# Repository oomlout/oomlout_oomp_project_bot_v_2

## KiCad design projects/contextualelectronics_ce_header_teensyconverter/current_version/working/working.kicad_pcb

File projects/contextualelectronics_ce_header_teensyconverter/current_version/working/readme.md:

# ce_header
 
## summary 
* id: contextualelectronics_ce_header_teensyconverter
* user: contextualelectronics
* name: ce_header
* board: teensyconverter
* repo: https://github.com/ContextualElectronics/CE-Header
* src_file_repo_kicad_pcb: TeensyConverter/TeensyConverter.kicad_pcb
* src_file_repo_kicad_pcb_link: https://github.com/ContextualElectronics/CE-Header/tree/master/TeensyConverter/TeensyConverter.kicad_pcb

* src_file_repo_sch: TeensyConverter/TeensyConverter.sch
* src_file_repo_sch_link: https://github.com/ContextualElectronics/CE-Header/tree/master/TeensyConverter/TeensyConverter.sch
* full details link: https://github.com/oomlout/oomlout_oomp_project_bot_v_2/tree/main/projects/contextualelectronics_ce_header_teensyconverter/current_version/working  

## schematic  
  
[schematic (pdf)](working_schematic.pdf) 

## pcb  

[board (pdf)](working.pdf)  

## working_bom
| Id | Designator | Footprint | Quantity | Designation | Supplier and ref |  | None | 
| --- | --- | --- | --- | --- | --- | --- | --- | 
| 1 | P1 | Pin_Header_Straight_1x03_Pitch2.54mm | 1 | CONN_01X03 |  |  | [''] | 
| 2 | R1,R2 | R_0805_HandSoldering | 2 | 0 |  |  | [''] | 
| 3 | U2 | CE_Header | 1 | CE_HEADER |  |  | [''] | 
| 4 | U1 | Teensy-32 | 1 | Teensy-3.2 |  |  | [''] | 

## bom_schematic
| Ref | Qnty | Value | Cmp name | Footprint | Description | Vendor | DNP | 
| --- | --- | --- | --- | --- | --- | --- | --- | 
| P1 | 1 | CONN_01X03 | CONN_01X03 | Pin_Headers:Pin_Header_Straight_1x03_Pitch2.54mm |  |  |  | 
| R1, R2 | 2 | 0 | R | Resistors_SMD:R_0805_HandSoldering |  |  |  | 
| U1 | 1 | Teensy-3.2 | Teensy-3.2 | TeensyConverter:Teensy-32 |  |  |  | 
| U2 | 1 | CE_HEADER | CE_HEADER | TeensyConverter:CE_Header |  |  |  |

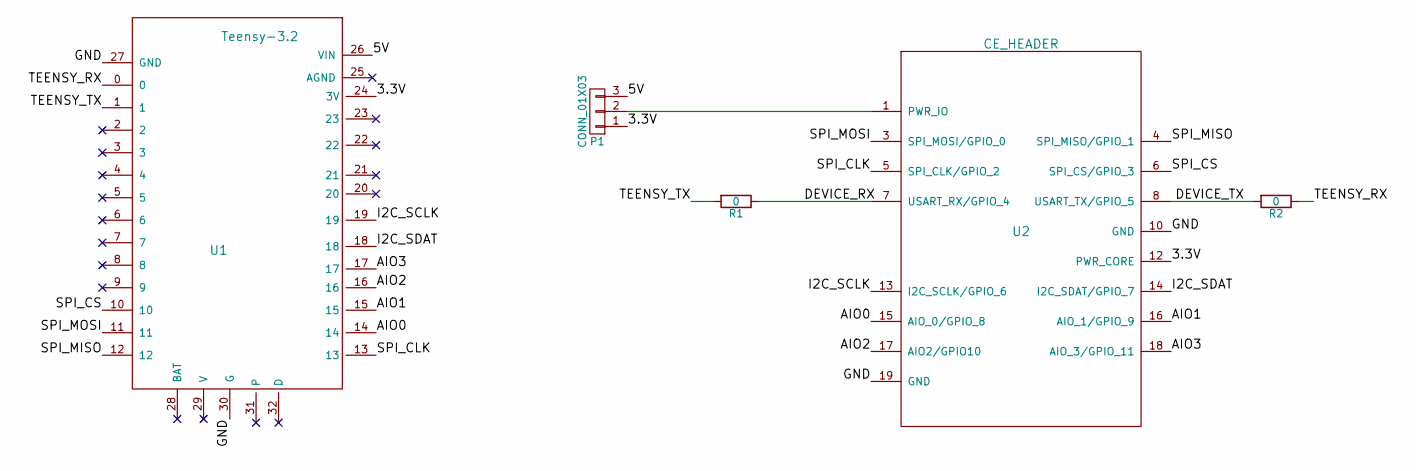
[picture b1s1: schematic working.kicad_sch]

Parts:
P1: CONN_01X03; Pin_Header_Straight_1x03_Pitch2.54mm
R1, R2: 0; R_0805_HandSoldering
U1: Teensy-3.2; Teensy-32
U2: CE_HEADER; CE_Header

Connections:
/3.3V: P1.1, U1.24 (3V), U2.12 (PWR_CORE)
/5V: P1.3, U1.26 (VIN)
/AIO0: U1.14, U2.15 (AIO_0/GPIO_8)
/AIO1: U1.15, U2.16 (AIO_1/GPIO_9)
/AIO2: U1.16, U2.17 (AIO2/GPIO10)
/AIO3: U1.17, U2.18 (AIO_3/GPIO_11)
/DEVICE_RX: R1.1, U2.7 (USART_RX/GPIO_4)
/DEVICE_TX: R2.2, U2.8 (USART_TX/GPIO_5)
/GND: U1.27 (GND), U1.30 (G), U2.10 (GND), U2.19 (GND)
/I2C_SCLK: U1.19, U2.13 (I2C_SCLK/GPIO_6)
/I2C_SDAT: U1.18, U2.14 (I2C_SDAT/GPIO_7)
/SPI_CLK: U1.13, U2.5 (SPI_CLK/GPIO_2)
/SPI_CS: U1.10, U2.6 (SPI_CS/GPIO_3)
/SPI_MISO: U1.12, U2.4 (SPI_MISO/GPIO_1)
/SPI_MOSI: U1.11, U2.3 (SPI_MOSI/GPIO_0)
/TEENSY_RX: R2.1, U1.0
/TEENSY_TX: R1.2, U1.1
unnamed: P1.2, U2.1 (PWR_IO)

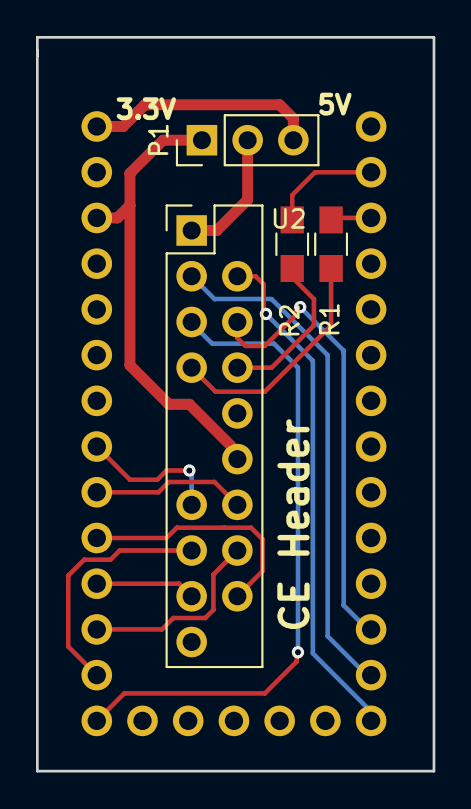
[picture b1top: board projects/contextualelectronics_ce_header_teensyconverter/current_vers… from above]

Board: 2 copper layers, 22.0 x 40.8 mm, 5 parts (1 on the bottom side), 18 nets.

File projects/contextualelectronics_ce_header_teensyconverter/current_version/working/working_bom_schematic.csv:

"Source:","C:\gh\oomlout_oomp_project_bot_v_2\projects\contextualelectronics_ce_header_teensyconverter\current_version\working\working.kicad_sch"
"Date:","19/09/2023 16:07:24"
"Tool:","Eeschema 7.0.6"
"Generator:","C:/Program Files/KiCad/7.0/bin/scripting/plugins/bom_csv_grouped_by_value_with_fp.py"
"Component Count:","5"
"Ref","Qnty","Value","Cmp name","Footprint","Description","Vendor","DNP"
"P1","1","CONN_01X03","CONN_01X03","Pin_Headers:Pin_Header_Straight_1x03_Pitch2.54mm","","",""
"R1, R2","2","0","R","Resistors_SMD:R_0805_HandSoldering","","",""
"U1","1","Teensy-3.2","Teensy-3.2","TeensyConverter:Teensy-32","","",""
"U2","1","CE_HEADER","CE_HEADER","TeensyConverter:CE_Header","","",""

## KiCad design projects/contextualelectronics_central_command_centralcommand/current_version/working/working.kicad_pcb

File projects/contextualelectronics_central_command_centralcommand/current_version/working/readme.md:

# central_command
 
## summary 
* id: contextualelectronics_central_command_centralcommand
* user: contextualelectronics
* name: central_command
* board: centralcommand
* repo: https://github.com/ContextualElectronics/Central-Command
* src_file_repo_kicad_pcb: Hardware/CentralCommand.kicad_pcb
* src_file_repo_kicad_pcb_link: https://github.com/ContextualElectronics/Central-Command/tree/master/Hardware/CentralCommand.kicad_pcb

* src_file_repo_sch: Hardware/CentralCommand.sch
* src_file_repo_sch_link: https://github.com/ContextualElectronics/Central-Command/tree/master/Hardware/CentralCommand.sch
* full details link: https://github.com/oomlout/oomlout_oomp_project_bot_v_2/tree/main/projects/contextualelectronics_central_command_centralcommand/current_version/working  

## schematic  
  
[schematic (pdf)](working_schematic.pdf) 

## pcb  

[board (pdf)](working.pdf)  

## working_bom
| Id | Designator | Footprint | Quantity | Designation | Supplier and ref |  | None | 
| --- | --- | --- | --- | --- | --- | --- | --- | 
| 1 | D301,D302 | Diode-SMA_Standard | 2 | D_Schottky |  |  | [''] | 
| 2 | D303,D304 | LED-0805 | 2 | LED |  |  | [''] | 
| 3 | L301 | Neosid_Inductor_SM1206 | 1 | FERRITE |  |  | [''] | 
| 4 | P101,P102 | Pin_Header_Straight_1x10 | 2 | CONN_01X10 |  |  | [''] | 
| 5 | P103,P105 | Pin_Header_Straight_1x04 | 2 | CONN_01X04 |  |  | [''] | 
| 6 | P104,P106,P302 | Pin_Header_Straight_1x02 | 3 | CONN_01X02 |  |  | [''] | 
| 7 | P201 | Pin_Header_Straight_1x06 | 1 | CONN_01X06 |  |  | [''] | 
| 8 | P204 | Pin_Header_Straight_1x03 | 1 | CONN_01X03 |  |  | [''] | 
| 9 | U101 | LQFP-48_7x7mm_Pitch0.5mm | 1 | STM32F030C8 |  |  | [''] | 
| 10 | U301 | SOT-23 | 1 | MCP1700T-3302E/TT_ |  |  | [''] | 
| 11 | U302 | QFN-32-1EP_5x5mm_Pitch0.5mm | 1 | FT232RQ |  |  | [''] | 
| 12 | Y101 | Crystal_HC49-U_Vertical | 1 | Crystal |  |  | [''] | 
| 13 | P301 | 10118193 | 1 | USB_B |  |  | [''] | 
| 14 | P202,P203 | Grove-2mm | 2 | CONN_01X04 |  |  | [''] | 
| 15 | SW201 | FSM2JSMAA-ND | 1 | FSM2JSMAA-ND |  |  | [''] | 
| 16 | REF**,REF**,REF**,REF** | MountingHole_3mm | 4 | MountingHole_3mm |  |  | [''] | 
| 17 | C101,C201 | C_0805 | 2 | C |  |  | [''] | 
| 18 | C102,C103 | C_0805 | 2 | 20P |  |  | [''] | 
| 19 | C301,C302,C304,C104,C107 | C_0805 | 5 | .1U |  |  | [''] | 
| 20 | C303 | C_1210 | 1 | 4.7U |  |  | [''] | 
| 21 | C305,C306 | C_1210 | 2 | 10U |  |  | [''] | 
| 22 | L101 | Neosid_Inductor_SM1206 | 1 | INDUCTOR |  |  | [''] | 
| 23 | R201,R202,R204 | R_0805 | 3 | R |  |  | [''] | 
| 24 | R203,R301,R302,R303,R206,R207,R208,R209 | R_0805 | 8 | 0 |  |  | [''] | 
| 25 | R304,R305 | R_0805 | 2 | NOPE |  |  | [''] | 
| 26 | R306,R307 | R_0805 | 2 | 270 |  |  | [''] | 
| 27 | C105,C108 | C_1206 | 2 | 1U |  |  | [''] | 
| 28 | C106,C109 | C_1206 | 2 | 10U |  |  | [''] | 
| 29 | G*** | CClogo-small | 1 | LOGO |  |  | [''] | 

## bom_schematic
| Ref | Qnty | Value | Cmp name | Footprint | Description | Vendor | DNP | 
| --- | --- | --- | --- | --- | --- | --- | --- | 
| C101, C104, C107 | 3 | .1U | C | Capacitors_SMD:C_0805 |  |  |  | 
| C102, C103 | 2 | 20P | C | Capacitors_SMD:C_0805 |  |  |  | 
| C105, C108 | 2 | 1U | C | Capacitors_SMD:C_1206 |  |  |  | 
| C106, C109 | 2 | 10U | C | Capacitors_SMD:C_1206 |  |  |  | 
| L101 | 1 | 10uH | INDUCTOR | Inductors_NEOSID:Neosid_Inductor_SM1206 |  |  |  | 
| P101, P102 | 2 | CONN_01X10 | CONN_01X10 | Pin_Headers:Pin_Header_Straight_1x10 |  |  |  | 
| P103, P105 | 2 | CONN_01X04 | CONN_01X04 | Pin_Headers:Pin_Header_Straight_1x04 |  |  |  | 
| P104, P106 | 2 | CONN_01X02 | CONN_01X02 | Pin_Headers:Pin_Header_Straight_1x02 |  |  |  | 
| U101 | 1 | STM32F030C8 | STM32F030C8 | Housings_QFP:LQFP-48_7x7mm_Pitch0.5mm |  |  |  | 
| Y101 | 1 | Crystal | Crystal | Crystals:Crystal_HC49-U_Vertical |  |  |  | 

## mounting_holes
| x | y | package | value | ref | size | 
| --- | --- | --- | --- | --- | --- | 
| 0.06 | 44.17 | MountingHole_3mm | MountingHole_3mm | REF** | m3 | 
| 0.0 | 0.0 | MountingHole_3mm | MountingHole_3mm | REF** | m3 | 
| 44.23 | 0.0 | MountingHole_3mm | MountingHole_3mm | REF** | m3 | 
| 44.18 | 44.15 | MountingHole_3mm | MountingHole_3mm | REF** | m3 |

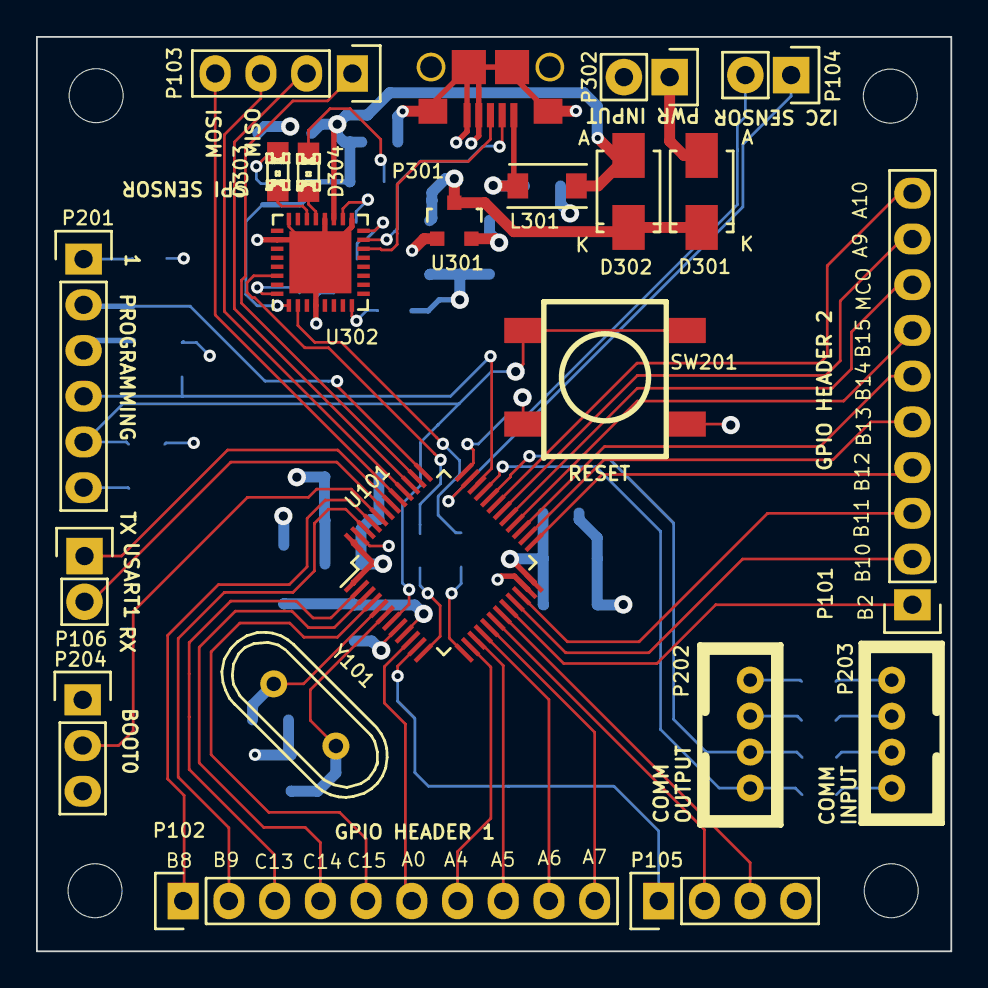
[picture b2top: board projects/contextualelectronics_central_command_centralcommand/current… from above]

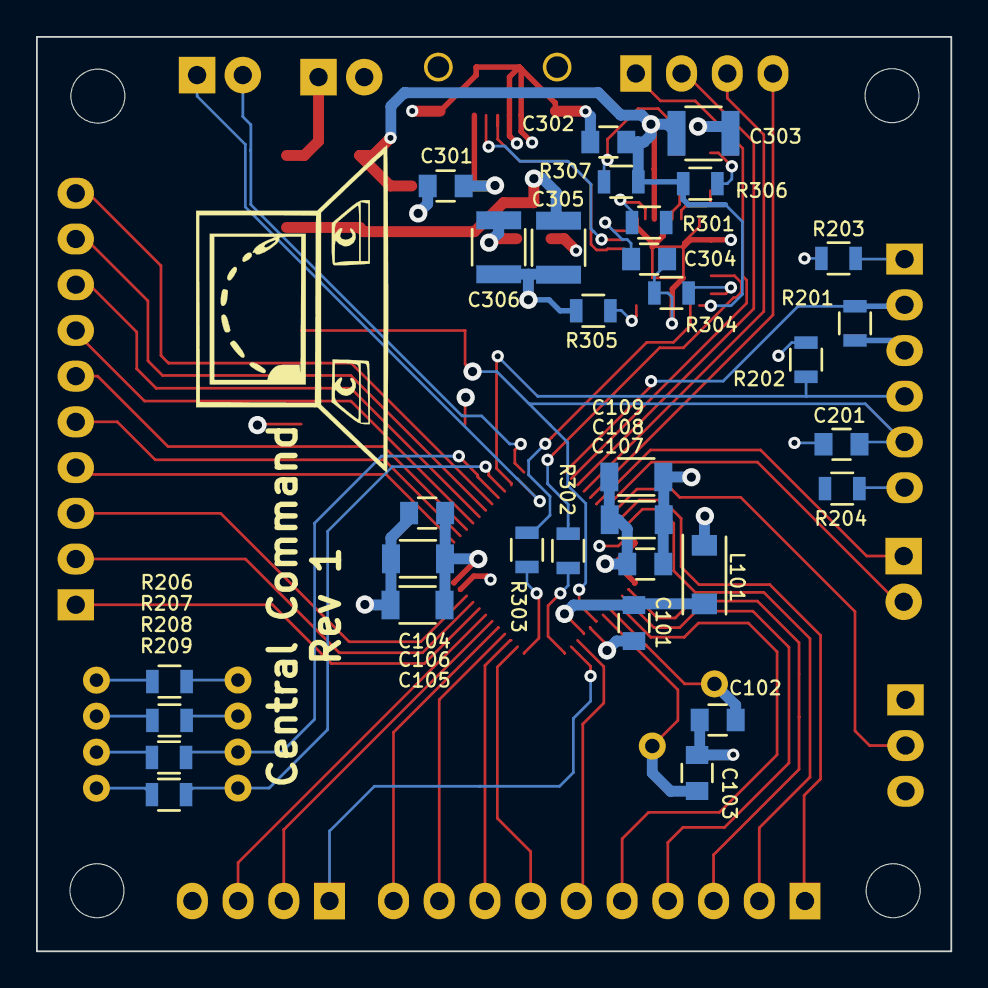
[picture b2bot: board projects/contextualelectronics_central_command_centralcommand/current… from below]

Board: 4 copper layers, 50.8 x 50.8 mm, 54 parts (32 on the bottom side), 66 nets.

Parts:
C101, C201: C; C_0805
C102, C103: 20P; C_0805
C104, C107, C301, C302, C304: .1U; C_0805
C105, C108: 1U; C_1206
C106, C109: 10U; C_1206
C303: 4.7U; C_1210
C305, C306: 10U; C_1210
D301, D302: D_Schottky; Diode-SMA_Standard
D303, D304: LED; LED-0805
L101: INDUCTOR; Neosid_Inductor_SM1206
L301: FERRITE; Neosid_Inductor_SM1206
P101, P102: CONN_01X10; Pin_Header_Straight_1x10
P103, P105: CONN_01X04; Pin_Header_Straight_1x04
P104, P106, P302: CONN_01X02; Pin_Header_Straight_1x02
P201: CONN_01X06; Pin_Header_Straight_1x06
P202, P203: CONN_01X04; Grove-2mm
P204: CONN_01X03; Pin_Header_Straight_1x03
P301: USB_B; 10118193
R201, R202, R204: R; R_0805
R203, R206, R207, R208, R209, R301, R302, R303: 0; R_0805
R304, R305: NOPE; R_0805
R306, R307: 270; R_0805
SW201: FSM2JSMAA-ND
U101: STM32F030C8; LQFP-48_7x7mm_Pitch0.5mm
U301: MCP1700T-3302E/TT_; SOT-23
U302: FT232RQ; QFN-32-1EP_5x5mm_Pitch0.5mm
Y101: Crystal; Crystal_HC49-U_Vertical

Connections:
/ADC_IN1: P105.1, U101.11
/ADC_IN8: P105.2, U101.18
/ADC_IN9: P105.3, U101.19
/Comm/BOOT0: P204.2, U101.44
/Comm/NRST: C201.1, P201.5, SW201.1, U101.7
/Comm/PWR: C104.1, C105.1, C106.1, C107.1, C108.1, C109.1, C306.1, L101.1, P202.2, P204.1, R202.1, R203.1, R207.1, U101.1, U101.24, U101.48, U301.2
/Comm/SCL: P202.3, R208.1, U101.32
/Comm/SDA: P202.4, R209.1, U101.33
/Comm/SWCLK: P201.2, R201.1, U101.37
/Comm/SWIO: P201.4, R202.2, U101.34
/I2C1_SCL: P104.2, U101.36
/I2C1_SDA: P104.1, U101.35
/MCO: P101.8, U101.29
/PA0: P102.6, U101.10
/PA4: P102.7, U101.14
/PA5: P102.8, U101.15
/PA6: P102.9, U101.16
/PA7: P102.10, U101.17
/PA9: P101.9, U101.30
/PA10: P101.10, U101.31
/PB2: P101.1, U101.20
/PB8: P102.1, U101.45
/PB9: P102.2, U101.46
/PB10: P101.2, U101.21
/PB11: P101.3, U101.22
/PB12: P101.4, U101.25
/PB13: P101.5, U101.26
/PB14: P101.6, U101.27
/PB15: P101.7, U101.28
/PC13: P102.3, U101.2
/PC14: P102.4, U101.3
/PC15: P102.5, U101.4
/Power/RXD: R303.1, U101.13
/Power/TXD: R302.1, U101.12
/Power/VCCIO: C302.1, C303.1, D302.2, L301.2, R306.1, R307.1, U302.1, U302.19
/SPI1_MISO: P103.3, U101.40
/SPI1_MOSI: P103.4, U101.41
/SPI1_NSS: P103.1, U101.38
/SPI1_SCK: P103.2, U101.39
/USART1_RX: P106.2, U101.43
/USART1_TX: P106.1, U101.42
/VDDA: C101.1, L101.2, U101.9
GND: C101.2, C102.1, C103.1, C104.2, C105.2, C106.2, C107.2, C108.2, C109.2, C201.2, C301.2, C302.2, C303.2, C304.2, C305.2, C306.2, P105.4, P201.3, P202.1, P204.3, P301.4, P301.5, P301.6, P301.7, P301.8, P301.9, P302.2, R201.2, R206.1, R304.1, R305.1, SW201.2, U101.8, U101.23, U101.47, U301.1, U302.4, U302.17, U302.20, U302.24, U302.26, U302.33
unnamed: C102.2, U101.5, Y101.1
unnamed: C103.2, U101.6, Y101.2
unnamed: C301.1, L301.1, P301.1
unnamed: C304.1, U302.16
unnamed: C305.1, D301.1, D302.1, U301.3
unnamed: D301.2, P302.1
unnamed: D303.1, U302.22
unnamed: D303.2, R306.2
unnamed: D304.1, U302.21
unnamed: D304.2, R307.2
unnamed: P201.1, R203.2
unnamed: P201.6, R204.1
unnamed: P203.1, R209.2
unnamed: P203.2, R208.2
unnamed: P203.3, R207.2
unnamed: P203.4, R206.2
unnamed: P301.2, U302.15
unnamed: P301.3, U302.14
unnamed: R301.1, U302.18
unnamed: R302.2, U302.30
unnamed: R303.2, U302.2
unnamed: R304.2, U302.32
unnamed: R305.2, U302.8

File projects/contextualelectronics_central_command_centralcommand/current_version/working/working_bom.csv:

"Id";"Designator";"Footprint";"Quantity";"Designation";"Supplier and ref";
1;"D301,D302";"Diode-SMA_Standard";2;"D_Schottky";;;
2;"D303,D304";"LED-0805";2;"LED";;;
3;"L301";"Neosid_Inductor_SM1206";1;"FERRITE";;;
4;"P101,P102";"Pin_Header_Straight_1x10";2;"CONN_01X10";;;
5;"P103,P105";"Pin_Header_Straight_1x04";2;"CONN_01X04";;;
6;"P104,P106,P302";"Pin_Header_Straight_1x02";3;"CONN_01X02";;;
7;"P201";"Pin_Header_Straight_1x06";1;"CONN_01X06";;;
8;"P204";"Pin_Header_Straight_1x03";1;"CONN_01X03";;;
9;"U101";"LQFP-48_7x7mm_Pitch0.5mm";1;"STM32F030C8";;;
10;"U301";"SOT-23";1;"MCP1700T-3302E/TT_";;;
11;"U302";"QFN-32-1EP_5x5mm_Pitch0.5mm";1;"FT232RQ";;;
12;"Y101";"Crystal_HC49-U_Vertical";1;"Crystal";;;
13;"P301";"10118193";1;"USB_B";;;
14;"P202,P203";"Grove-2mm";2;"CONN_01X04";;;
15;"SW201";"FSM2JSMAA-ND";1;"FSM2JSMAA-ND";;;
16;"REF**,REF**,REF**,REF**";"MountingHole_3mm";4;"MountingHole_3mm";;;
17;"C101,C201";"C_0805";2;"C";;;
18;"C102,C103";"C_0805";2;"20P";;;
19;"C301,C302,C304,C104,C107";"C_0805";5;".1U";;;
20;"C303";"C_1210";1;"4.7U";;;
21;"C305,C306";"C_1210";2;"10U";;;
22;"L101";"Neosid_Inductor_SM1206";1;"INDUCTOR";;;
23;"R201,R202,R204";"R_0805";3;"R";;;
24;"R203,R301,R302,R303,R206,R207,R208,R209";"R_0805";8;"0";;;
25;"R304,R305";"R_0805";2;"NOPE";;;
26;"R306,R307";"R_0805";2;"270";;;
27;"C105,C108";"C_1206";2;"1U";;;
28;"C106,C109";"C_1206";2;"10U";;;
29;"G***";"CClogo-small";1;"LOGO";;;

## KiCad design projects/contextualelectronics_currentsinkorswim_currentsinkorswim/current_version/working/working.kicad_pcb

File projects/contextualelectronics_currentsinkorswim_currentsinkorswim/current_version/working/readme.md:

# currentsinkorswim
 
## summary 
* id: contextualelectronics_currentsinkorswim_currentsinkorswim
* user: contextualelectronics
* name: currentsinkorswim
* board: currentsinkorswim
* repo: https://github.com/ContextualElectronics/CurrentSinkOrSwim
* src_file_repo_kicad_pcb: CurrentSinkOrSwim.kicad_pcb
* src_file_repo_kicad_pcb_link: https://github.com/ContextualElectronics/CurrentSinkOrSwim/tree/master/CurrentSinkOrSwim.kicad_pcb

* src_file_repo_sch: 
* src_file_repo_sch_link: https://github.com/ContextualElectronics/CurrentSinkOrSwim/tree/master/
* full details link: https://github.com/oomlout/oomlout_oomp_project_bot_v_2/tree/main/projects/contextualelectronics_currentsinkorswim_currentsinkorswim/current_version/working  

## schematic  
  
[schematic (pdf)](working_schematic.pdf) 

## pcb  

[board (pdf)](working.pdf)  

## working_bom
| Id | Designator | Footprint | Quantity | Designation | Supplier and ref |  | None | 
| --- | --- | --- | --- | --- | --- | --- | --- | 
| 1 | D201 | SOD-523 | 1 | DIODE |  |  | [''] | 
| 2 | Q401 | TO-220_FET-GDS_Vertical | 1 | BUK9575 |  |  | [''] | 
| 3 | R201 | SMD-0805 | 1 | 28.7K |  |  | [''] | 
| 4 | R202 | SMD-0805 | 1 | 9K |  |  | [''] | 
| 5 | R301 | SMD-0805 | 1 | 0 |  |  | [''] | 
| 6 | R302 | SMD-0805 | 1 | 27K |  |  | [''] | 
| 7 | R403 | Resistor_Horizontal_RM15mm | 1 | .1 |  |  | [''] | 
| 8 | U201 | SOIC-8-N | 1 | LMV358 |  |  | [''] | 
| 9 | U301 | SOIC-8-N | 1 | LM2931D-R |  |  | [''] | 
| 10 | P1 | FA-T220-38E | 1 | CONN_01X01 |  |  | [''] | 
| 11 | P101,P103 | Terminal_Block_200_mil | 2 | CONN_01X02 |  |  | [''] | 
| 12 | P102 | Pin_Header_Straight_1x03 | 1 | CONN_01X03 |  |  | [''] | 
| 13 | RV201,RV401 | P090L-02F25BR10K | 2 | 10K |  |  | [''] | 
| 14 | R203,R402 | SMD-0805 | 2 | 1K |  |  | [''] | 
| 15 | R303 | SMD-0805 | 1 | 21.6K |  |  | [''] | 
| 16 | G*** | CSOS | 1 | LOGO |  |  | [''] | 
| 17 | C201,C301,C302 | SMD-0805 | 3 | C |  |  | [''] | 
| 18 | R401 | SMD-0805 | 1 | 68K |  |  | [''] | 

## bom_schematic
| Ref | Qnty | Value | Cmp name | Footprint | Description | Vendor | DNP | 
| --- | --- | --- | --- | --- | --- | --- | --- | 
| P101, P103 | 2 | CONN_01X02 | CONN_01X02 | Current:Terminal_Block_200_mil |  |  |  | 
| P102 | 1 | CONN_01X03 | CONN_01X03 | Pin_Headers:Pin_Header_Straight_1x03 |  |  |  |

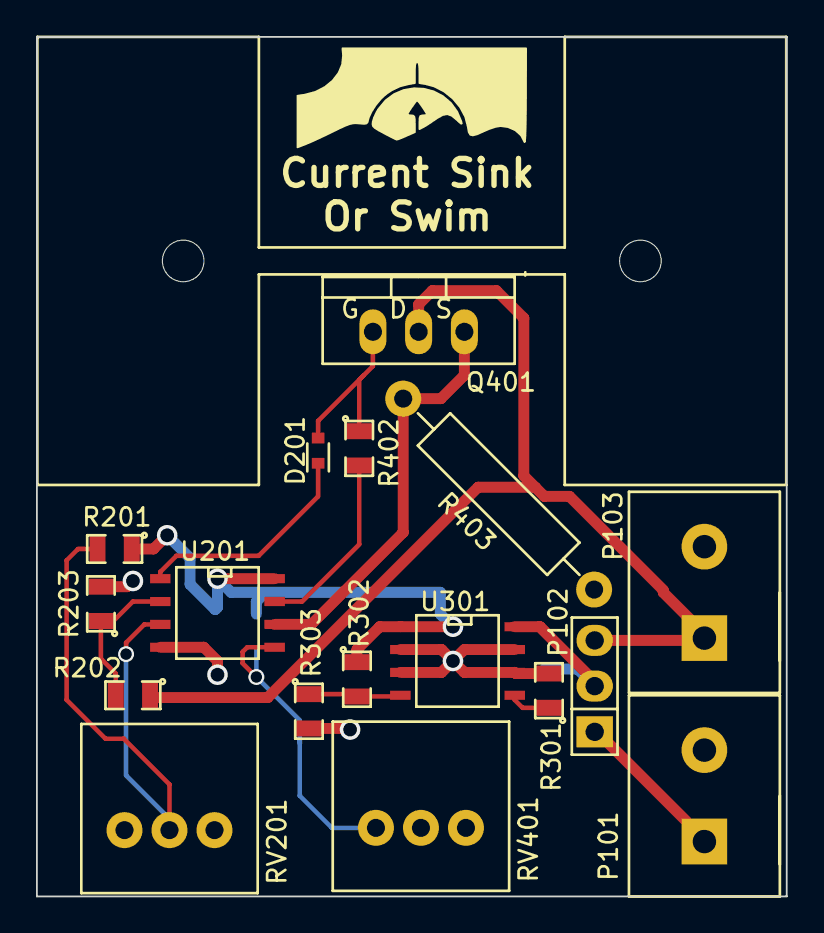
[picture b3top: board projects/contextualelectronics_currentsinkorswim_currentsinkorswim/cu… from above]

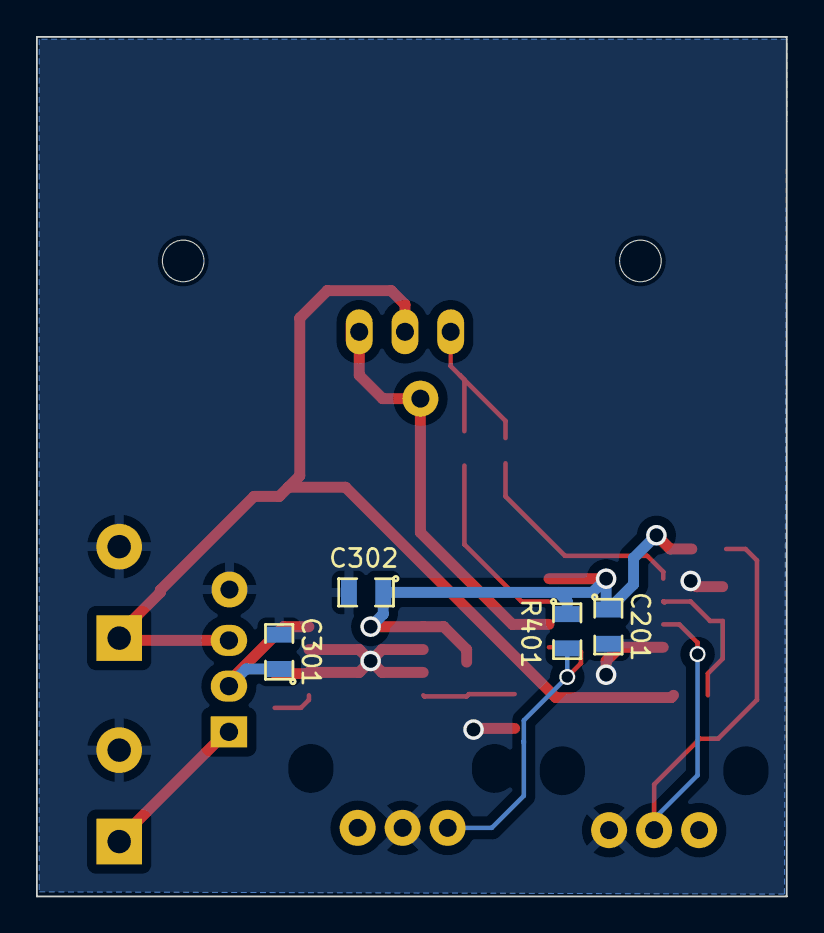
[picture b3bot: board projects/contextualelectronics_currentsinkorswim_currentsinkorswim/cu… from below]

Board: 2 copper layers, 41.7 x 47.8 mm, 22 parts (4 on the bottom side), 14 nets.

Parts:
C201, C301, C302: C; SMD-0805
D201: DIODE; SOD-523
P1: CONN_01X01; FA-T220-38E
P101, P103: CONN_01X02; Terminal_Block_200_mil
P102: CONN_01X03; Pin_Header_Straight_1x03
Q401: BUK9575; TO-220_FET-GDS_Vertical
R201: 28.7K; SMD-0805
R202: 9K; SMD-0805
R203, R402: 1K; SMD-0805
R301: 0; SMD-0805
R302: 27K; SMD-0805
R303: 21.6K; SMD-0805
R401: 68K; SMD-0805
R403: .1; Resistor_Horizontal_RM15mm
RV201, RV401: 10K; P090L-02F25BR10K
U201: LMV358; SOIC-8-N
U301: LM2931D-R; SOIC-8-N

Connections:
2.7V: C201.1, C302.1, R201.1, R302.1, R401.1, U201.8, U301.1
/Current Control/Current_Sink+: P102.3, P103.1, Q401.D, R202.1
/Current Control/FET_Gate: D201.1, Q401.G, R402.1
/Power Regulation/Vin: C301.1, P102.2, U301.8
GND: C201.2, C301.2, C302.2, P101.2, P103.2, R203.2, R301.2, R303.2, R403.2, RV201.3, RV401.2, U201.4, U301.2, U301.3, U301.6, U301.7
unnamed: D201.2, U201.1
unnamed: P101.1, P102.1
unnamed: Q401.S, R403.1, U201.6
unnamed: R201.2, RV201.2, U201.3
unnamed: R202.2, R203.1, U201.2
unnamed: R301.1, U301.5
unnamed: R302.2, R303.1, U301.4
unnamed: R401.2, RV401.1, U201.5
unnamed: R402.2, U201.7

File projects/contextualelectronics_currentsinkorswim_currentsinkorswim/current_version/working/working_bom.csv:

"Id";"Designator";"Footprint";"Quantity";"Designation";"Supplier and ref";
1;"D201";"SOD-523";1;"DIODE";;;
2;"Q401";"TO-220_FET-GDS_Vertical";1;"BUK9575";;;
3;"R201";"SMD-0805";1;"28.7K";;;
4;"R202";"SMD-0805";1;"9K";;;
5;"R301";"SMD-0805";1;"0";;;
6;"R302";"SMD-0805";1;"27K";;;
7;"R403";"Resistor_Horizontal_RM15mm";1;".1";;;
8;"U201";"SOIC-8-N";1;"LMV358";;;
9;"U301";"SOIC-8-N";1;"LM2931D-R";;;
10;"P1";"FA-T220-38E";1;"CONN_01X01";;;
11;"P101,P103";"Terminal_Block_200_mil";2;"CONN_01X02";;;
12;"P102";"Pin_Header_Straight_1x03";1;"CONN_01X03";;;
13;"RV201,RV401";"P090L-02F25BR10K";2;"10K";;;
14;"R203,R402";"SMD-0805";2;"1K";;;
15;"R303";"SMD-0805";1;"21.6K";;;
16;"G***";"CSOS";1;"LOGO";;;
17;"C201,C301,C302";"SMD-0805";3;"C";;;
18;"R401";"SMD-0805";1;"68K";;;

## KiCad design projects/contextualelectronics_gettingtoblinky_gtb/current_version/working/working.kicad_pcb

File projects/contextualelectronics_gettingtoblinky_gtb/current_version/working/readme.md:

# gettingtoblinky
 
## summary 
* id: contextualelectronics_gettingtoblinky_gtb
* user: contextualelectronics
* name: gettingtoblinky
* board: gtb
* repo: https://github.com/ContextualElectronics/GettingToBlinky
* src_file_repo_kicad_pcb: GTB.kicad_pcb
* src_file_repo_kicad_pcb_link: https://github.com/ContextualElectronics/GettingToBlinky/tree/master/GTB.kicad_pcb

* src_file_repo_sch: GTB.sch
* src_file_repo_sch_link: https://github.com/ContextualElectronics/GettingToBlinky/tree/master/GTB.sch
* full details link: https://github.com/oomlout/oomlout_oomp_project_bot_v_2/tree/main/projects/contextualelectronics_gettingtoblinky_gtb/current_version/working  

## schematic  
  
[schematic (pdf)](working_schematic.pdf) 

## pcb  

[board (pdf)](working.pdf)  

## working_bom
| Id | Designator | Footprint | Quantity | Designation | Supplier and ref |  | None | 
| --- | --- | --- | --- | --- | --- | --- | --- | 
| 1 | U1 | SO8N | 1 | 7555 |  |  | [''] | 
| 2 | R1 | SM1206 | 1 | 470K |  |  | [''] | 
| 3 | R2 | SM1206 | 1 | 1K |  |  | [''] | 
| 4 | VR1 | R1 | 1 | LDR |  |  | [''] | 
| 5 | D1 | LED-1206 | 1 | LED |  |  | [''] | 
| 6 | C1 | SM1206 | 1 | 1U |  |  | [''] | 
| 7 | BT1 | CR2032 | 1 | CR2032 |  |  | [''] | 

## bom_schematic
| Ref | Qnty | Value | Cmp name | Footprint | Description | Vendor | DNP | 
| --- | --- | --- | --- | --- | --- | --- | --- | 
| BT1 | 1 | CR2032 | BATTERY |  |  |  |  | 
| C1 | 1 | 1U | C |  |  |  |  | 
| D1 | 1 | LED | LED |  |  |  |  | 
| R1 | 1 | 470K | R |  |  |  |  | 
| R2 | 1 | 1K | R |  |  |  |  | 
| U1 | 1 | 7555 | 7555 |  |  |  |  | 
| VR1 | 1 | LDR | VR |  |  |  |  |

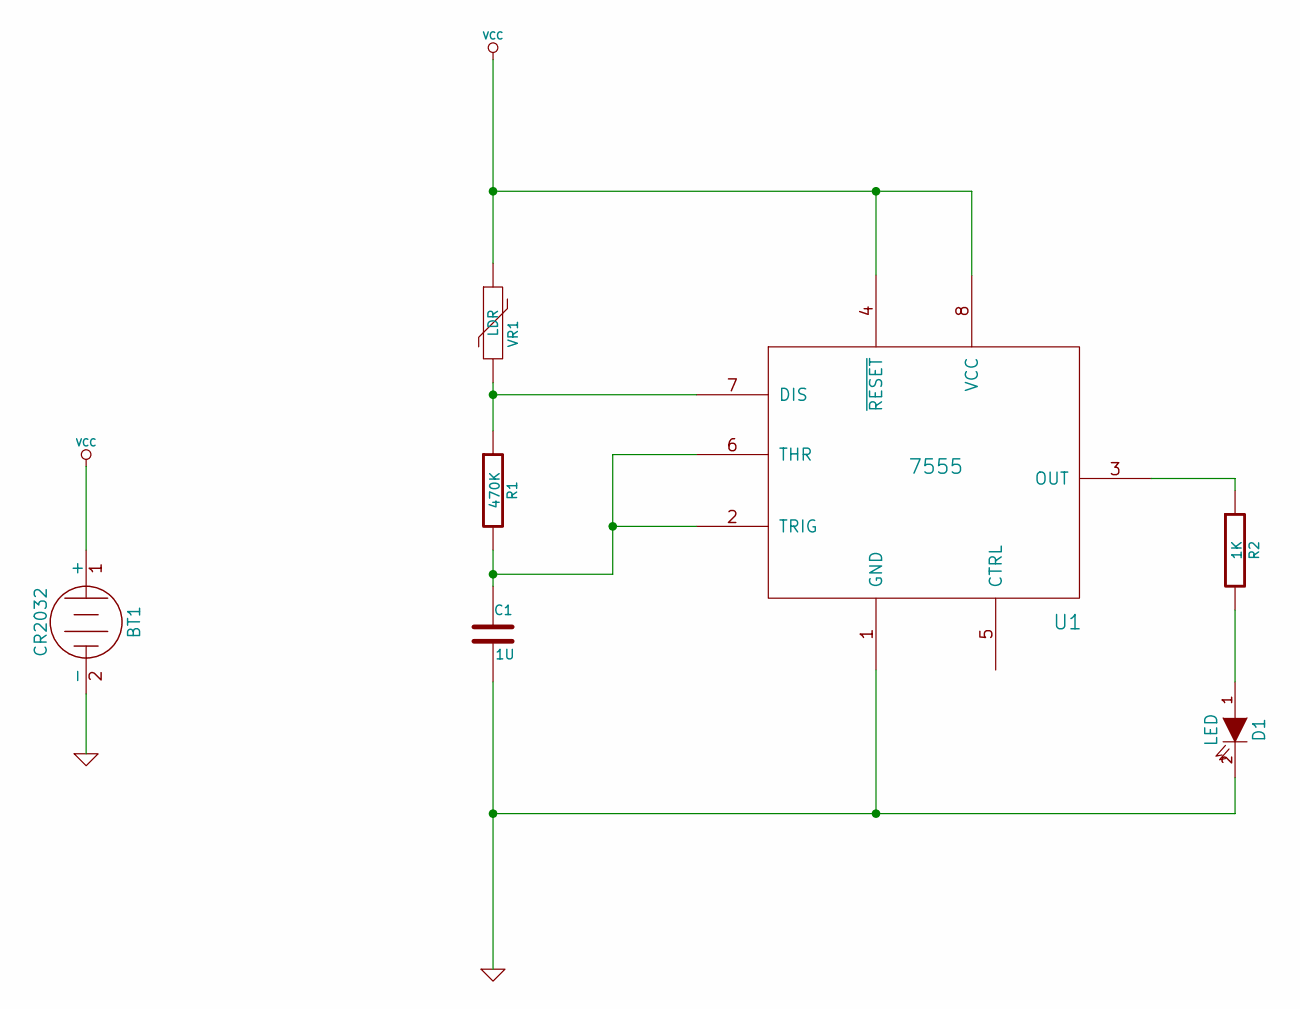
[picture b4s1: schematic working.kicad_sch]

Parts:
BT1: CR2032
C1: 1U
D1: LED
R1: 470K
R2: 1K
U1: 7555
VR1: LDR

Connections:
GND: BT1.2 (-), C1.2, D1.2 (K), U1.1 (GND)
unnamed: D1.1 (A), R2.2
unnamed: R2.1, U1.3 (OUT)
unnamed: C1.1, R1.2, U1.2 (TRIG), U1.6 (THR)
unnamed: R1.1, U1.7 (DIS), VR1.2
VCC: BT1.1 (+), U1.4 (~RESET), U1.8 (VCC), VR1.1

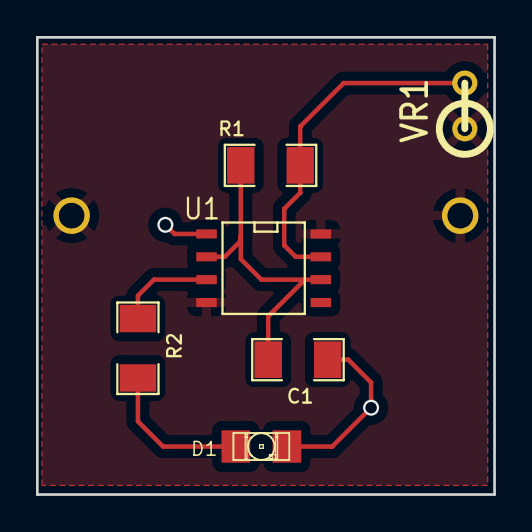
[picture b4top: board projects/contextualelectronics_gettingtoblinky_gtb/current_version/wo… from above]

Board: 2 copper layers, 25.4 x 25.4 mm, 7 parts (1 on the bottom side), 6 nets.

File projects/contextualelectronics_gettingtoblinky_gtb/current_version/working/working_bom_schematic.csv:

"Source:","C:\gh\oomlout_oomp_project_bot_v_2\projects\contextualelectronics_gettingtoblinky_gtb\current_version\working\working.kicad_sch"
"Date:","19/09/2023 16:45:40"
"Tool:","Eeschema 7.0.6"
"Generator:","C:/Program Files/KiCad/7.0/bin/scripting/plugins/bom_csv_grouped_by_value_with_fp.py"
"Component Count:","7"
"Ref","Qnty","Value","Cmp name","Footprint","Description","Vendor","DNP"
"BT1","1","CR2032","BATTERY","","","",""
"C1","1","1U","C","","","",""
"D1","1","LED","LED","","","",""
"R1","1","470K","R","","","",""
"R2","1","1K","R","","","",""
"U1","1","7555","7555","","","",""
"VR1","1","LDR","VR","","","",""

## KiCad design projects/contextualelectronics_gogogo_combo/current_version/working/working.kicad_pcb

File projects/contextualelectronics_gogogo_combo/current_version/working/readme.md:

# gogogo
 
## summary 
* id: contextualelectronics_gogogo_combo
* user: contextualelectronics
* name: gogogo
* board: combo
* repo: https://github.com/ContextualElectronics/GoGoGo
* src_file_repo_kicad_pcb: Combo.kicad_pcb
* src_file_repo_kicad_pcb_link: https://github.com/ContextualElectronics/GoGoGo/tree/master/Combo.kicad_pcb

* src_file_repo_sch: 
* src_file_repo_sch_link: https://github.com/ContextualElectronics/GoGoGo/tree/master/
* full details link: https://github.com/oomlout/oomlout_oomp_project_bot_v_2/tree/main/projects/contextualelectronics_gogogo_combo/current_version/working  

## pcb  

[board (pdf)](working.pdf)  

## working_bom
| Id | Designator | Footprint | Quantity | Designation | Supplier and ref |  | None | 
| --- | --- | --- | --- | --- | --- | --- | --- | 
| 1 | C1,C3 | C_0805 | 2 | .1U |  |  | [''] | 
| 2 | C2,C4 | C_1206 | 2 | 10U |  |  | [''] | 
| 3 | P1,P3,P1,P2 | Pin_Header_Straight_1x02 | 4 | CONN_01X02 |  |  | [''] | 
| 4 | P2 | Pin_Header_Straight_1x04 | 1 | CONN_01X04 |  |  | [''] | 
| 5 | U1 | SSOP-20 | 1 | TB6593FNG |  |  | [''] | 
| 6 | C1 | C_0805_HandSoldering | 1 | C |  |  | [''] | 
| 7 | R1 | R_0805_HandSoldering | 1 | 100 |  |  | [''] | 
| 8 | R2,R3,R4,R5 | R_0805_HandSoldering | 4 | 1K |  |  | [''] | 
| 9 | TP1 | Measurement_Point_Round-SMD-Pad_Small | 1 | OptoOut |  |  | [''] | 
| 10 | U2 | SOIC-8_3.9x4.9mm_Pitch1.27mm | 1 | LM311N |  |  | [''] | 
| 11 | U1 | RPI-579N1 | 1 | RPI-579N1 |  |  | [''] | 
| 12 | REF**,REF** | MouseBite | 2 | MouseBite |  |  | [''] |

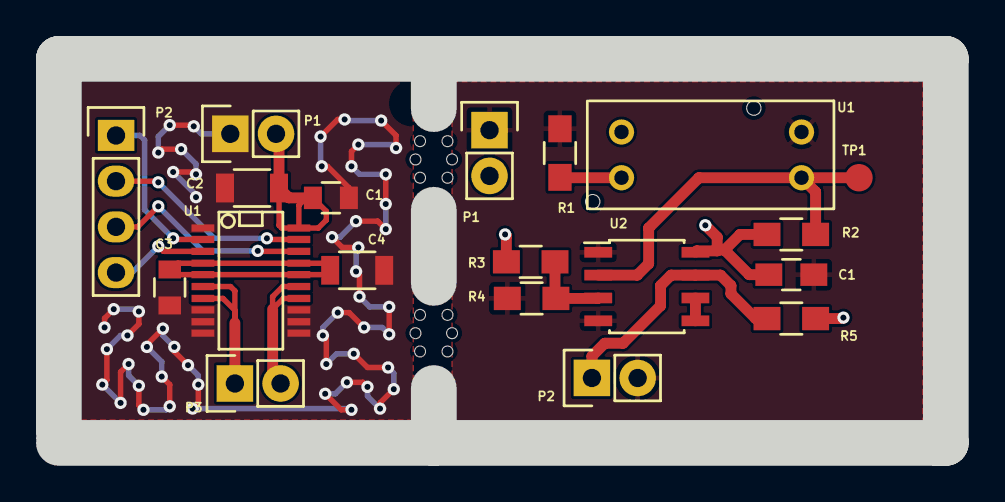
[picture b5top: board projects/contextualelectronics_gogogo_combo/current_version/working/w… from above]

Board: 2 copper layers, 49.3 x 21.3 mm, 19 parts (0 on the bottom side), 15 nets.

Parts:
C1, C3: .1U; C_0805
C1#2: C; C_0805_HandSoldering
C2, C4: 10U; C_1206
P1, P1#2, P2#2, P3: CONN_01X02; Pin_Header_Straight_1x02
P2: CONN_01X04; Pin_Header_Straight_1x04
R1: 100; R_0805_HandSoldering
R2, R3, R4, R5: 1K; R_0805_HandSoldering
TP1: OptoOut; Measurement_Point_Round-SMD-Pad_Small
U1: TB6593FNG; SSOP-20
U1#2: RPI-579N1
U2: LM311N; SOIC-8_3.9x4.9mm_Pitch1.27mm

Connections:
/IN1: P2.3, U1.18
/IN2: P2.2, U1.19
/O1: P3.1, U1.6, U1.7
/O2: P3.2, U1.14, U1.15
/PWM: P2.1, U1.2
/STBY: P2.4, U1.3
/VCC: C1.1, C2.1, P1.2, U1.20
/VM: C3.1, C4.1, U1.4, U1.5, U1.16, U1.17
GND: C1.2, C1#2.2, C2.2, C3.2, C4.2, P1.1, P1#2.1, P2#2.2, R1.2, R4.2, U1.1, U1.8, U1.9, U1.10, U1.11, U1.12, U1.13, U1#2.4, U2.1, U2.4
unnamed: P2#2.1, R5.2, U2.7
unnamed: R1.1, U1#2.2
unnamed: R2.2, TP1.1, U1#2.3, U2.2
unnamed: R3.2, R4.1, U2.3
unnamed: U2.5, U2.6
VCC: C1#2.1, P1#2.2, R2.1, R3.1, R5.1, U1#2.1, U2.8

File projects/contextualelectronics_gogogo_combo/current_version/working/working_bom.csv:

"Id";"Designator";"Footprint";"Quantity";"Designation";"Supplier and ref";
1;"C1,C3";"C_0805";2;".1U";;;
2;"C2,C4";"C_1206";2;"10U";;;
3;"P1,P3,P1,P2";"Pin_Header_Straight_1x02";4;"CONN_01X02";;;
4;"P2";"Pin_Header_Straight_1x04";1;"CONN_01X04";;;
5;"U1";"SSOP-20";1;"TB6593FNG";;;
6;"C1";"C_0805_HandSoldering";1;"C";;;
7;"R1";"R_0805_HandSoldering";1;"100";;;
8;"R2,R3,R4,R5";"R_0805_HandSoldering";4;"1K";;;
9;"TP1";"Measurement_Point_Round-SMD-Pad_Small";1;"OptoOut";;;
10;"U2";"SOIC-8_3.9x4.9mm_Pitch1.27mm";1;"LM311N";;;
11;"U1";"RPI-579N1";1;"RPI-579N1";;;
12;"REF**,REF**";"MouseBite";2;"MouseBite";;;

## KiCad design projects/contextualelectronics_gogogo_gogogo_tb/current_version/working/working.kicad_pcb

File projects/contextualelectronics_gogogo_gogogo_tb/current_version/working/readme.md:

# gogogo
 
## summary 
* id: contextualelectronics_gogogo_gogogo_tb
* user: contextualelectronics
* name: gogogo
* board: gogogo_tb
* repo: https://github.com/ContextualElectronics/GoGoGo
* src_file_repo_kicad_pcb: MotorDriver-TB6593/GoGoGo-TB.kicad_pcb
* src_file_repo_kicad_pcb_link: https://github.com/ContextualElectronics/GoGoGo/tree/master/MotorDriver-TB6593/GoGoGo-TB.kicad_pcb

* src_file_repo_sch: MotorDriver-TB6593/GoGoGo-TB.sch
* src_file_repo_sch_link: https://github.com/ContextualElectronics/GoGoGo/tree/master/MotorDriver-TB6593/GoGoGo-TB.sch
* full details link: https://github.com/oomlout/oomlout_oomp_project_bot_v_2/tree/main/projects/contextualelectronics_gogogo_gogogo_tb/current_version/working  

## schematic  
  
[schematic (pdf)](working_schematic.pdf) 

## pcb  

[board (pdf)](working.pdf)  

## working_bom
| Id | Designator | Footprint | Quantity | Designation | Supplier and ref |  | None | 
| --- | --- | --- | --- | --- | --- | --- | --- | 
| 1 | C1,C3 | C_0805 | 2 | .1U |  |  | [''] | 
| 2 | C2,C4 | C_1206 | 2 | 10U |  |  | [''] | 
| 3 | P2 | Pin_Header_Straight_1x04 | 1 | CONN_01X04 |  |  | [''] | 
| 4 | P3 | Pin_Header_Straight_1x02 | 1 | CONN_01X02 |  |  | [''] | 
| 5 | U1 | SSOP-20 | 1 | TB6593FNG |  |  | [''] | 
| 6 | D1,D2,D3,D4 | LED-0805 | 4 | LED |  |  | [''] | 
| 7 | R5 | R_0805_HandSoldering | 1 | 0 |  |  | [''] | 
| 8 | P1 | Pin_Header_Straight_1x03 | 1 | CONN_01X03 |  |  | [''] | 
| 9 | REF**,REF**11,REF**11,REF** | MountingHole_3mm | 4 | MountingHole_3mm |  |  | [''] | 
| 10 | REF**111,REF**121,REF**131,REF**141,REF**151,REF**112,REF**122,REF**132,REF**142,REF**152,REF**113,REF**123,REF**133,REF**143,REF**153,REF**114,REF**124,REF**134,REF**144,REF**154,REF**115,REF**125,REF**135,REF**145,REF**155,REF**1511,REF**1521,REF**1531,REF**1541,REF**1551,REF**1561,REF**1571,REF**1581,REF**1512,REF**1522,REF**1532,REF**1542,REF**1552,REF**1562,REF**1572,REF**1582,REF**1513,REF**1523,REF**1533,REF**1543,REF**1553,REF**1563,REF**1573,REF**1583,REF**1514,REF**1524,REF**1534,REF**1544,REF**1554,REF**1564,REF**1574,REF**1584,REF**1515,REF**1525,REF**1535,REF**1545,REF**1555,REF**1565,REF**1575,REF**1585,REF**1516,REF**1526,REF**1536,REF**1546,REF**1556,REF**1566,REF**1576,REF**1586,REF**1517,REF**1527,REF**1537,REF**1547,REF**1557,REF**1567,REF**1577,REF**1587,REF**1518,REF**1528,REF**1538,REF**1548,REF**1558,REF**1568,REF**1578,REF**1588,REF**155111,REF**155121,REF**155131,REF**155112,REF**155122,REF**155132,REF**155113,REF**155123,REF**155133,REF**155114,REF**155124,REF**155134 | Via | 101 | Via |  |  | [''] | 
| 11 | R1,R2,R3,R4 | R_0805_HandSoldering | 4 | 1K |  |  | [''] | 

## bom_schematic
| Ref | Qnty | Value | Cmp name | Footprint | Description | Vendor | DNP | 
| --- | --- | --- | --- | --- | --- | --- | --- | 
| C1, C3 | 2 | .1U | C | Capacitors_SMD:C_0805 |  |  |  | 
| C2, C4 | 2 | 10U | C | Capacitors_SMD:C_1206 |  |  |  | 
| D1, D2, D3, D4 | 4 | LED | LED | LEDs:LED-0805 |  |  |  | 
| P1 | 1 | CONN_01X03 | CONN_01X03 | Pin_Headers:Pin_Header_Straight_1x03 |  |  |  | 
| P2 | 1 | CONN_01X04 | CONN_01X04 | Pin_Headers:Pin_Header_Straight_1x04 |  |  |  | 
| P3 | 1 | CONN_01X02 | CONN_01X02 | Pin_Headers:Pin_Header_Straight_1x02 |  |  |  | 
| R1, R2, R3, R4 | 4 | 1K | R | Resistors_SMD:R_0805_HandSoldering |  |  |  | 
| R5 | 1 | 0 | R | Resistors_SMD:R_0805_HandSoldering |  |  |  | 
| U1 | 1 | TB6593FNG | TB6593FNG | SMD_Packages:SSOP-20 |  |  |  | 

## mounting_holes
| x | y | package | value | ref | size | 
| --- | --- | --- | --- | --- | --- | 
| 19.69 | 22.86 | MountingHole_3mm | MountingHole_3mm | REF** | m3 | 
| 19.69 | 0.0 | MountingHole_3mm | MountingHole_3mm | REF** | m3 | 
| 0.0 | 22.86 | MountingHole_3mm | MountingHole_3mm | REF**11 | m3 | 
| 0.0 | 0.0 | MountingHole_3mm | MountingHole_3mm | REF**11 | m3 |

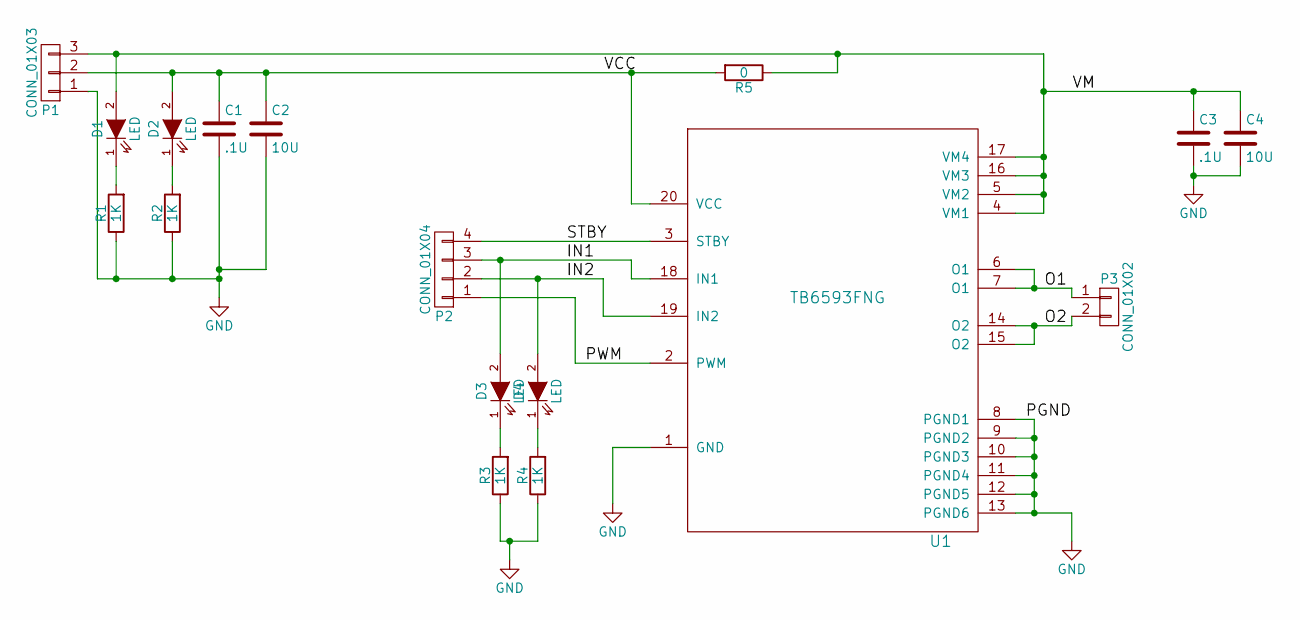
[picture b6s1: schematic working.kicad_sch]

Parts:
C1, C3: .1U; C_0805
C2, C4: 10U; C_1206
D1, D2, D3, D4: LED; LED-0805
P1: CONN_01X03; Pin_Header_Straight_1x03
P2: CONN_01X04; Pin_Header_Straight_1x04
P3: CONN_01X02; Pin_Header_Straight_1x02
R1, R2, R3, R4: 1K; R_0805_HandSoldering
R5: 0; R_0805_HandSoldering
U1: TB6593FNG; SSOP-20; MPN TB6593FNG

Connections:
/IN1: D3.2 (A), P2.3, U1.18 (IN1)
/IN2: D4.2 (A), P2.2, U1.19 (IN2)
/O1: P3.1, U1.6 (O1), U1.7 (O1)
/O2: P3.2, U1.14 (O2), U1.15 (O2)
/PWM: P2.1, U1.2 (PWM)
/STBY: P2.4, U1.3 (STBY)
/VCC: C1.1, C2.1, D2.2 (A), P1.2, R5.2, U1.20 (VCC)
/VM: C3.1, C4.1, D1.2 (A), P1.3, R5.1, U1.4 (VM1), U1.5 (VM2), U1.16 (VM3), U1.17 (VM4)
GND: C1.2, C2.2, C3.2, C4.2, P1.1, R1.1, R2.1, R3.1, R4.1, U1.1 (GND), U1.8 (PGND1), U1.9 (PGND2), U1.10 (PGND3), U1.11 (PGND4), U1.12 (PGND5), U1.13 (PGND6)
unnamed: D1.1 (K), R1.2
unnamed: D2.1 (K), R2.2
unnamed: D3.1 (K), R3.2
unnamed: D4.1 (K), R4.2

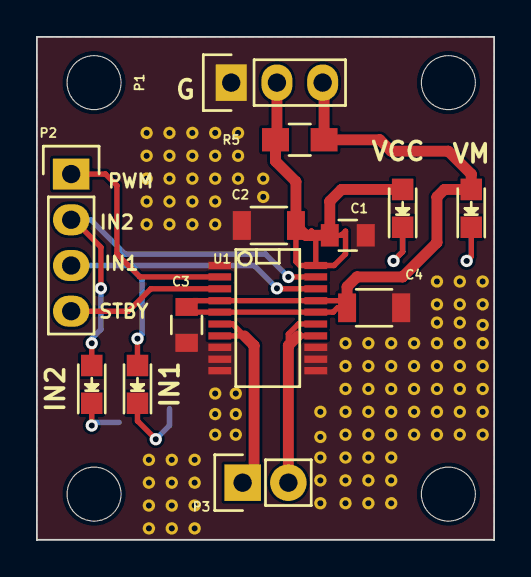
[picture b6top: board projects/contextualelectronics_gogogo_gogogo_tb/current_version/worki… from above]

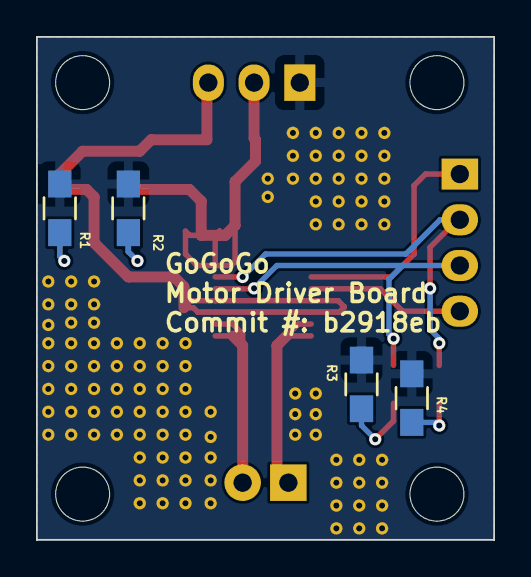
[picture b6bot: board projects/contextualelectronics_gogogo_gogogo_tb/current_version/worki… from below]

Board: 2 copper layers, 25.4 x 27.9 mm, 17 parts (4 on the bottom side), 13 nets.

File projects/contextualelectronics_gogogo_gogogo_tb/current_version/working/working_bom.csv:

"Id";"Designator";"Footprint";"Quantity";"Designation";"Supplier and ref";
1;"C1,C3";"C_0805";2;".1U";;;
2;"C2,C4";"C_1206";2;"10U";;;
3;"P2";"Pin_Header_Straight_1x04";1;"CONN_01X04";;;
4;"P3";"Pin_Header_Straight_1x02";1;"CONN_01X02";;;
5;"U1";"SSOP-20";1;"TB6593FNG";;;
6;"D1,D2,D3,D4";"LED-0805";4;"LED";;;
7;"R5";"R_0805_HandSoldering";1;"0";;;
8;"P1";"Pin_Header_Straight_1x03";1;"CONN_01X03";;;
9;"REF**,REF**11,REF**11,REF**";"MountingHole_3mm";4;"MountingHole_3mm";;;
10;"REF**111,REF**121,REF**131,REF**141,REF**151,REF**112,REF**122,REF**132,REF**142,REF**152,REF**113,REF**123,REF**133,REF**143,REF**153,REF**114,REF**124,REF**134,REF**144,REF**154,REF**115,REF**125,REF**135,REF**145,REF**155,REF**1511,REF**1521,REF**1531,REF**1541,REF**1551,REF**1561,REF**1571,REF**1581,REF**1512,REF**1522,REF**1532,REF**1542,REF**1552,REF**1562,REF**1572,REF**1582,REF**1513,REF**1523,REF**1533,REF**1543,REF**1553,REF**1563,REF**1573,REF**1583,REF**1514,REF**1524,REF**1534,REF**1544,REF**1554,REF**1564,REF**1574,REF**1584,REF**1515,REF**1525,REF**1535,REF**1545,REF**1555,REF**1565,REF**1575,REF**1585,REF**1516,REF**1526,REF**1536,REF**1546,REF**1556,REF**1566,REF**1576,REF**1586,REF**1517,REF**1527,REF**1537,REF**1547,REF**1557,REF**1567,REF**1577,REF**1587,REF**1518,REF**1528,REF**1538,REF**1548,REF**1558,REF**1568,REF**1578,REF**1588,REF**155111,REF**155121,REF**155131,REF**155112,REF**155122,REF**155132,REF**155113,REF**155123,REF**155133,REF**155114,REF**155124,REF**155134";"Via";101;"Via";;;
11;"R1,R2,R3,R4";"R_0805_HandSoldering";4;"1K";;;
